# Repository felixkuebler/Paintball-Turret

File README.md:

Paintball Turret
=====================

A turret to aim and shoot paintballs.
Controlled via webinterface.

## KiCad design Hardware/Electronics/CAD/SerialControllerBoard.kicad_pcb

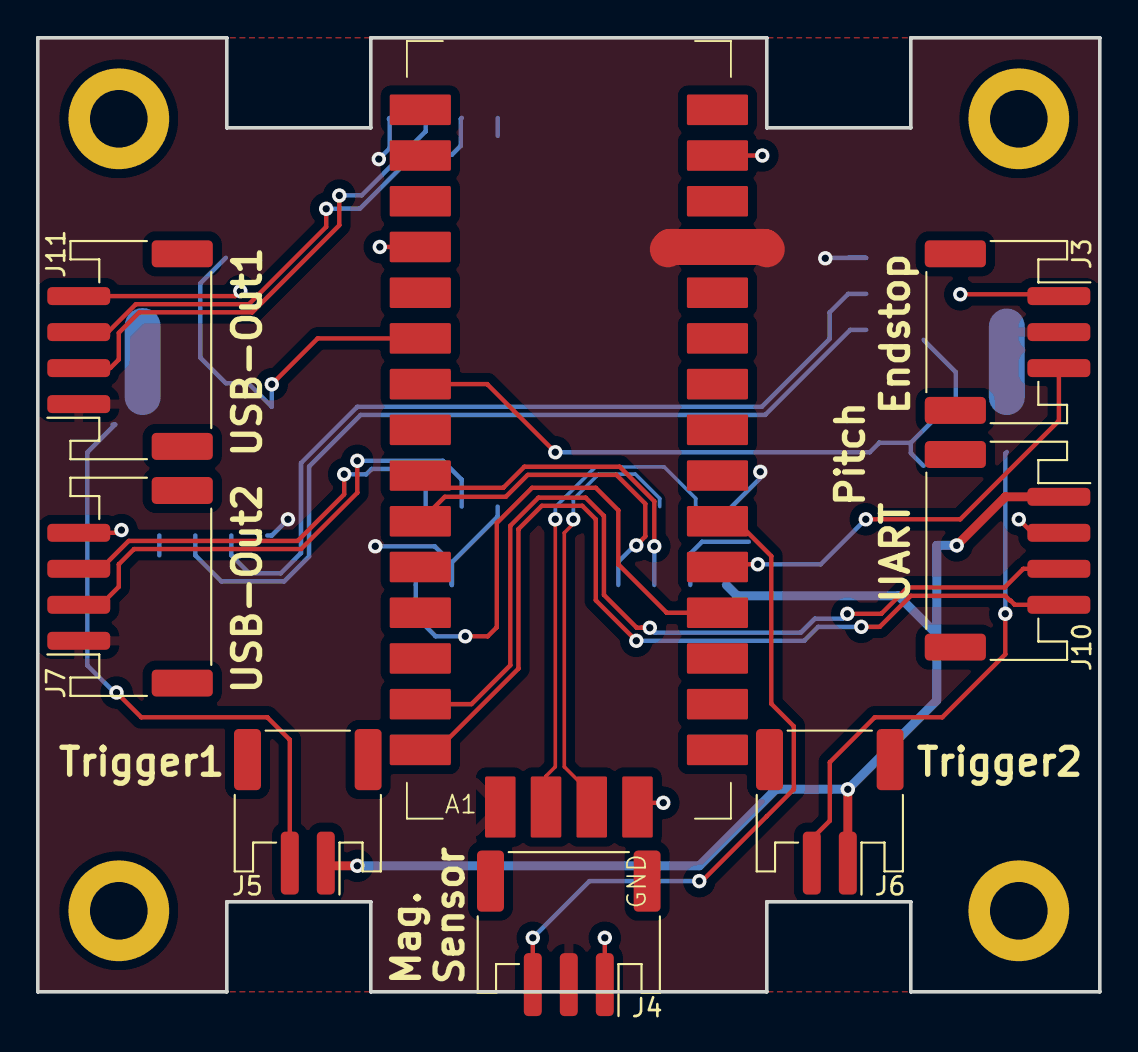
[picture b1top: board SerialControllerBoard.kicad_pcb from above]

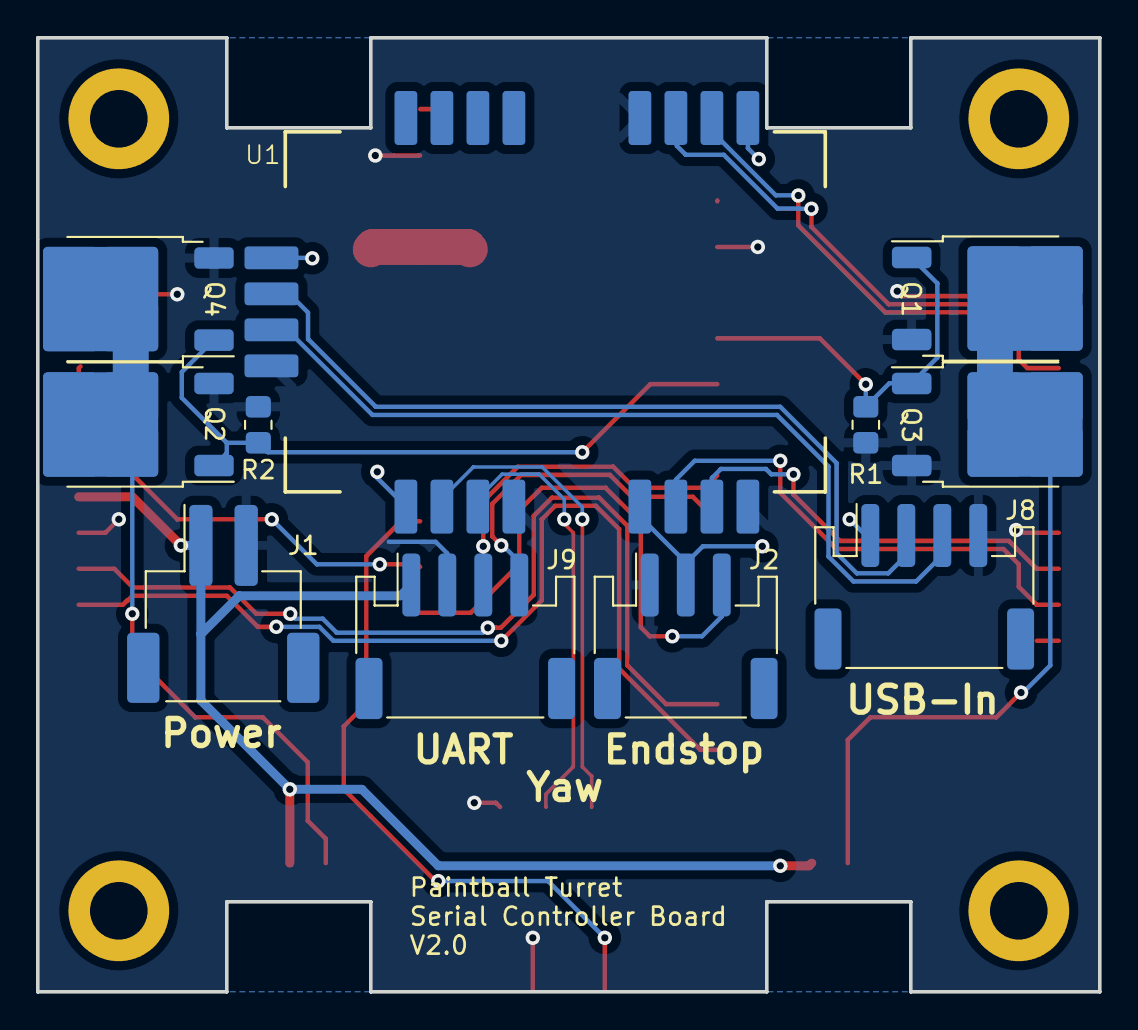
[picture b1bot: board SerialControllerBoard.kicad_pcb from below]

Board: 2 copper layers, 59.0 x 53.0 mm, 23 parts (11 on the bottom side), 22 nets.

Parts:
A1: Arduino_Nano_v3.x; Arduino_Nano_SoM
H1, H2, H3, H4: MountingHole; MountingHole_3.2mm_M3_DIN965_Pad
J1: Conn_01x02; JST_XH_S2B-XH-SM4-TB_1x02-1MP_P2.50mm_Horizontal
J2, J3, J4: Conn_01x03; JST_PH_S3B-PH-SM4-TB_1x03-1MP_P2.00mm_Horizontal
J5, J6: Conn_01x02; JST_PH_S2B-PH-SM4-TB_1x02-1MP_P2.00mm_Horizontal
J7, J8, J9, J10, J11: Conn_01x04; JST_PH_S4B-PH-SM4-TB_1x04-1MP_P2.00mm_Horizontal
Q1, Q2, Q3, Q4: D4184; TO-252-2
R1, R2: 10k; R_0805_2012Metric_Pad1.20x1.40mm_HandSolder
U1: FE11SX4

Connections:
+5V: A1.27 (+5V), A1.31 (USB-V5), J2.2, J3.2, J4.2, J7.1, J8.1, J11.1, U1.1 (IN-5V), U1.5 (OUT1-5V), U1.9 (OUT2-5V), U1.13 (OUT3-5V)
GND: A1.4 (GND), A1.29 (GND), A1.34 (USB-GND), J1.2, J2.1, J3.1, J4.1, J7.4, J8.4, J9.2, J10.2, J11.4, Q1.3 (S), Q2.3 (S), Q3.3 (S), Q4.3 (S), R1.2, R2.2, U1.4 (IN-GND), U1.8 (OUT1-GND), U1.12 (OUT2-GND), U1.16 (OUT3-GND)
unnamed: J5.2, Q1.2 (D), Q3.2 (D)
unnamed: J6.2, Q2.2 (D), Q4.2 (D)
unnamed: J7.2, U1.10 (OUT2-D-)
unnamed: J7.3, U1.11 (OUT2-D+)
unnamed: J8.2, U1.2 (IN-D-)
unnamed: J8.3, U1.3 (IN-D+)
unnamed: J11.2, U1.14 (OUT3-D-)
unnamed: J11.3, U1.15 (OUT3-D+)
USB-D+: A1.33 (USB-D+), U1.7 (OUT1-D+)
USB-D-: A1.32 (USB-D-), U1.6 (OUT1-D-)
VCC: J1.1, J5.1, J6.1, J9.1, J10.1
endstop-pitch: A1.20 (A1), J3.3
endstop-yaw: A1.19 (A0), J2.3
mag-sensor: A1.21 (A2), J4.3
pitch-uart-rx: A1.14 (D11), J10.3
pitch-uart-tx: A1.15 (D12), J10.4
trigger-primary: A1.6 (D3), Q1.1 (G), Q3.1 (G), R1.1
trigger-secondary: A1.7 (D4), Q2.1 (G), Q4.1 (G), R2.1
yaw-uart-rx: A1.9 (D6), J9.3
yaw-uart-tx: A1.10 (D7), J9.4

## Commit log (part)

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2020-11-18 changed the range input style, position feedback is also forwarted to range inputs
2020-11-18 invert y position of feedback
2020-11-19 styling html file
2020-11-19 range slider knob image
2020-11-19 handle style request from static folder
2020-11-19 changes static path
2020-11-19 request file not location
2020-11-19 new approach for image file in static style
2020-11-19 static file routing
2020-11-19 fiddle with style path
2020-11-19 another approach on static files
2020-11-19 reactivate position feedback
2020-11-19 new img folder for html images
2020-11-19 separate html from css and js
2020-11-20 cleanup style and dark mode
2020-11-20 different image containers for preview and fullscreen
2020-11-20 test images for turret position overview
2020-11-20 no maxima for speedcontrolle
2020-11-22 apply dark mode changes to chrome
2020-11-22 position indicator images for x
2020-11-22 image rotation function
2020-11-22 reinclude mouse movement as controle for direction speed
2020-11-22 remove angular controlle as primary motion controlle
2020-11-22 do not load image for each iteration
2020-11-22 different sizes for html sections
2020-11-23 new turret icons for position feedback
2020-11-23 center of rotation axis for dynamic images
2020-11-23 test paths for includes and x,y position indicator (currently wrong scale)
2020-11-23 old file naming convention
2020-11-23 add draw function for position feedback overview
2020-11-23 debugging path removed from css import
2020-11-23 debugging references removed from js
2020-11-23 image is not loaded completely when accessed
2020-11-23 images are still not loaded when accessed
2020-11-23 fixed path for image import
2020-11-23 enable position feedback
2020-11-23 debugging stange bug in draw.js
2020-11-23 changing input trigger and feedback direction
2020-11-23 moving const definitions into main file
2020-11-23 remove declarations from html
2020-11-23 input for mobile devices
2020-11-23 improved controlls
2020-11-24 final cleanup of html style
2020-11-24 change back to greyscale -> easier to see
2020-11-24 back coordinates for light background
2020-11-24 maximum position printed depending on size of crosshair
2020-11-24 put calibration button on bottom of html page
2020-11-24 invert mobile x controls
2020-11-24 add mobile screen corner description
2020-11-24 if trigger is not reset all input will be triggering the trigger function
2020-11-24 try to use camera for multi-client purposes
2020-11-24 sed paramter mixed with path variables
2020-11-24 different separators for sed
2020-11-24 did not save auto start file
2020-11-24 installation only uses generic variables
2020-11-24 different port for docker image and hostname chage in installation
2020-11-24 makefile option for internal and external port
2020-11-24 internal and external ports switched
2020-11-25 add joystick to html
2020-11-25 scaling issue of position display fixed
2020-11-25 display joystick functionality added
2020-11-25 joystick added to touch html
2020-11-25 commit joystick image files
2020-11-25 changes joystick parameters
2020-11-25 scaing issue due to loading page while mobile phone is not rotated
2020-11-25 joystick with binary input
2020-11-26 map function for linear functions
2020-11-26 different speed scale
2020-11-26 better edge case for y speed control
2020-11-26 comment server output
2020-11-26 only use integer values to not oversend commands
2020-11-26 different speeds for y axis
2020-11-26 speed change for y up
2020-11-26 extrem parameters for bug fixing
2020-11-26 other way around
2020-11-26 round function at wrong position
2020-12-03 courser wasnt hidden in fullscreen mode
2020-12-04 installation for autostart console only boot
2024-07-05 move tests into dedicated folder
2024-07-05 add thermal camera test
2024-07-09 improve thermal camera read with 16bit input in test
2024-07-09 Add thermal camera to main project
2024-07-09 rename cameraDevice to rgbCamera
    wip
    wip
2024-07-09 add color map selection to html
2024-07-09 include definition in serial device class
2024-07-09 spelling fixes
2024-07-09 improve thermal camera read with 16bit input
    wip
2024-07-09 add grey scale to color maps
2024-07-09 add camera selector
2024-07-09 add styling for select-option elements
2024-07-09 add color map display
2024-07-09 add normaization to thermal imaging
2024-07-09 add abs range to thermal imaging
2024-07-09 add hybrid cmaera test
2024-07-19 change datatype of testImage
2024-07-23 Add thermal camera datasheet to repo
2024-07-23 remove motor options
2024-07-23 replace old cmd defines with update cmds
2024-07-23 cleanup style
2024-07-23 remove old cpr motor struct
    wip
    wip remove motor struct
    wip
2024-07-23 add stepper motor config
    wip motor config
    wip
2024-07-28 adapt userInput test
2024-07-28 adapt serial commands
2024-07-28 finalize pitch parameters
2024-07-28 add absolute position to arduinoDevice
2024-07-28 remove unused code from arduinoDevice
2024-07-29 add docker installation to makefile
2024-07-29 remove Turret file and replace with direct calls to arduinoSerialDevice
2024-07-29 adjust numpy read from deprecated version
2024-07-29 add restart command to makefile
2024-07-29 match rgb roi and thermal frame
2024-07-29 change thermal calera absolute temperature range
2024-08-01 minimalize html view
2024-08-04 remove speed input temporarly
2024-08-04 invert position input
2024-08-04 use speed input for yaw
2024-08-04 dont use rgb roi for now
2024-08-05 fix style
2024-08-05 change naming convention from x,y to yaw,pitch
2024-08-05 add gamepad handling for speed
2024-08-05 apply rpm based on gear ratio
2024-08-05 adapt speed control to accept 0-100% speed only
2024-08-05 enable speed control via webserver
2024-08-05 better async handling of axis control
2024-08-05 etter async handling of axis control
2024-08-05 remove depricated code
2024-08-05 first working version of gamepad controls
2024-08-05 fix of the mapping function
2024-08-06 introduce zooming for the rgb camera
2024-08-06 post trigger command from gamepad
2024-08-08 write speed single command
2024-08-08 fix serial read
2024-08-08 revert uart buffer mistake
2024-08-18 increase baudrate for serial communication
2024-09-04 create new serial commands for primary and secondary triggers
2024-09-04 create new primary trigger functionality
2024-09-04 remove screen joystick input
2024-09-04 write speeds in single command
2024-09-04 increase serial baudrate in frontend
2024-09-04 adapt to new trigger serial commands in frontend
2024-09-10 Add Gamepad image files for website
2024-09-20 new gamepad icon files for the webpage
2024-09-26 Update damepad icons and add fullscreen icon
2024-09-26 use faster/simpler solenoid trigger
2024-09-26 add light and dark icons
2024-10-14 Add SerialController PCB electronics hardware
2024-10-16 Add Arduino and TMC 3D models to KiCad
2024-10-18 remove old deproicated code
2024-10-18 enable fullscreen with start button or dedicated button on livestream
2024-10-18 remove deprecated code
2024-10-18 add light icons to html
2024-10-18 change x/y Position to pitch/yaw notation
2024-10-18 enable rotation feedback
2024-10-18 simple working hybrid camera
2024-10-18 remove turret position overview icons
2024-10-18 change position poll to stream
2024-10-18 callback function for display and hide popup
2024-10-18 add controller camera and color map change
2024-10-18 change camera aspect ration
2024-10-18 change videoFeed spelling convention
2024-10-18 new and simpler style for the main UI
2024-10-18 adjust crosshair color and size
2024-10-18 Style: remove comments
2024-10-18 add infinite rotation scale for yaw
2024-11-14 new type of thermalcamera test implementation
2024-11-21 Improved 3D libraries for Ardiuno and TMC
2024-11-21 Switch pins for better cable management
2025-02-15 Add function to enable data stream remotely
2025-02-15 Fix comments
2025-02-15 Change name of streaming command
2025-02-15 improve absolute values of thermal image
2025-02-15 Adjust aim offset
2025-02-15 improved hybrid camera mux
2025-02-15 move Zoom into cameraMux
2025-02-15 Adjust web ui to mobile
2025-02-15 wip position stream
2025-02-15 move aim offset into cameraMux
2025-02-15 use nativ camera resolution and only scale in cameraMux
2025-02-15 adapt style to mobile and desktop
2025-02-15 handle long time no thermal read issue
2025-02-15 read 16bit and 8bit thermal image
2025-02-15 Use v4l2 for thermal camera frames
2025-02-15 add drop curve to crosshair
2025-02-15 makefile fixes
2025-02-15 Add threaded data streaming for position feedback
2025-03-01 Create endstop class to manage endstop behaviour
2025-03-01 Add settings icon for webpage
2025-03-01 Move pin definitions into motor config file
2025-03-01 Integrate pitch endstop for speedcontrol
2025-03-01 Update webpage icons
2025-03-01 add helper function to stepper drive to cache and read angles
2025-03-01 Create frontend for pitch calibration
2025-03-01 Integrate pitch calibration into backend
    wip
2025-06-19 Add yaw calibration sequence
2025-06-19 Style and comments
2025-06-19 Integrate pitch calibration into backend
2025-06-19 Create frontend for yaw calibration
2025-06-19 Bugfix for position feedback stream
2025-06-19 Bugfix ServoDriver used wrong direction for speed control
2025-10-24 Include FE11SX4 USB Hub modul into KiCad
2025-10-24 Add JST-XH 2Pin SMD footprint
2025-10-24 New controller board Layout with USB Hub and Arduino SoM
2025-10-24 Update Arduino MotorConfig to align with schematic
2025-10-24 Remove unnecessary files
2025-10-24 Update Gerber files
2025-11-28 Import Jst-PH SMD 3D libraries
2025-11-28 Import ArduinoNanoSoM 3D libraries
2025-11-28 Import UsbHub FE11SX4 3D libraries
2025-11-28 Reference correct 3D files to footprints
2025-11-28 Export 3D model of controller board
2025-12-13 Only start homing yaw if not already on home position
2025-12-13 invert pitch endstop direction
2025-12-17 Make different trigger types selectable via uart interface
2025-12-17 Create different TriggerTypes and a dedicated driver
2026-02-16 Change pith gear ratio to new hardware design
2026-02-27 Set Height of all icons to 300px
2026-02-27 Add trigger icons
2026-03-03 Reduce number of thermal color maps
2026-03-03 Add function to draw camera and trigger info onto fullscreen crosshair
2026-03-03 Cleanup draw.js file
2026-03-03 Fix crosshair line offsets
2026-03-03 Add trigger mode selector to GUI
2026-03-03 Fix camera and thermal selector references
2026-03-14 Add camera mux & selector
2026-03-14 Rename cameraDevice to rgbCamera
2026-03-14 Improve thermal camera read with 16bit input
2026-03-14 Add color map graphics
2026-03-14 Remove old CPR motor struct
2026-03-14 Add absolute position for stepper motor
2026-03-14 Replace old serial commands
2026-03-14 Remove unused CPR motor code from arduinoDevice
2026-03-14 Adapt serial commands in backend
2026-03-14 Add stepper motors
2026-03-14 Adapt userInput test to direct arduinoSerialDevice calls
2026-03-14 Add hybrid camera test
2026-03-14 Change thermal camera absolute temperature range
2026-03-14 Add gamepad to GUI for user input
2026-03-14 Remove old deprecated code and elements
2026-03-14 Minimalize html GUI
2026-03-14 Add speed control to backend
2026-03-14 Limit speed control to accept 0-100% speed only
2026-03-14 Use MultiDriver for better async two axis control
2026-03-14 Remove old screen joystick input
2026-03-14 Add zooming for the RGB camera
2026-03-14 Fix uart buffer bug
2026-03-14 Adapt code for fast solenoid trigger
2026-03-14 New commands for primary and secondary triggers
2026-03-14 New combi command for pitch and yaw speed
2026-03-14 Simpler style for the main UI
2026-03-14 Add Gamepad icons and overview image for website
2026-03-14 Enable fullscreen with start button or dedicated button on video feed
2026-03-14 Add fullscreen icons for website
2026-03-14 Change position feedback from polling to streaming
2026-03-14 Adjust aim offset in camera feed
2026-03-14 New v4l2 thermal camera test implementation
2026-03-14 Use native camera resolution and only scale in cameraMux
2026-03-14 Make docker executable without root
2026-03-14 Exclude build from main target
2026-03-14 Fix autostart
